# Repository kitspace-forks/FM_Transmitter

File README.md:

# FM Transmitter

This is the circuit built by Afrotechmods in this frequency modulation tutorial video.

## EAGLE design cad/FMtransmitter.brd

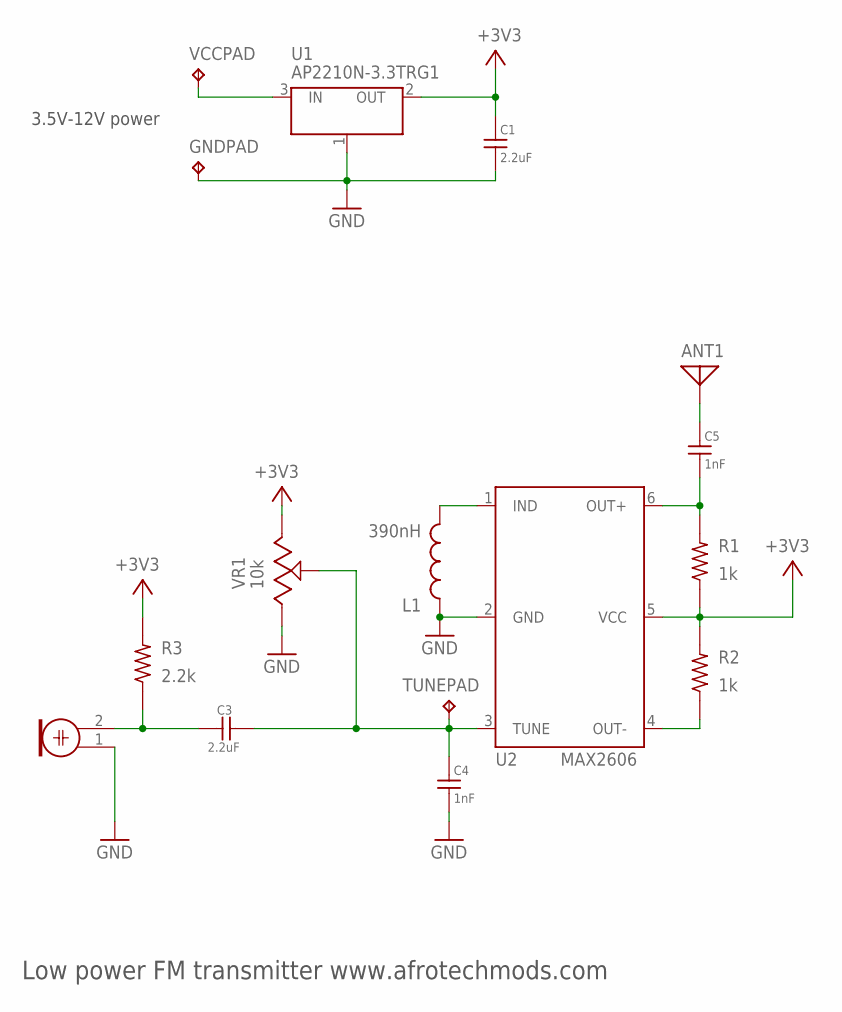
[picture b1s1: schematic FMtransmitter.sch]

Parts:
ANT1: ANTENNA; PAD-01
C1, C3: 2.2uF; 0805
C4, C5: 1nF; 0805
GNDPAD: TPPAD1-13; P1-13
L1: 390nH; 0805
MK1: ELECTRET_MICROPHON-WM-64PC/64PK; WM-64PC/64PK
R1, R2: 1k; 0805
R3: 2.2k; 0805
TUNEPAD: TPPAD1-13; P1-13
U1: AP2210N-3.3TRG1; SOT-23
U2: MAX2606; SOT23-6
VCCPAD: TPPAD1-13; P1-13
VR1: 10k; SMDPOT

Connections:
+3V3: C1.P$2 (2), R1.P$2 (2), R2.P$1 (1), R3.P$1 (1), U1.2 (OUT), U2.5 (VCC), VR1.3 (E)
GND: C1.P$1 (1), C4.P$1 (1), GNDPAD.TP, L1.P$1 (1), MK1.1, U1.1 (GND), U2.2 (GND), VR1.1 (A)
unnamed: L1.P$2 (2), U2.1 (IND)
unnamed: U1.3 (IN), VCCPAD.TP
unnamed: C5.P$1 (1), R1.P$1 (1), U2.6 (OUT+)
unnamed: R2.P$2 (2), U2.4 (OUT-)
unnamed: ANT1.1, C5.P$2 (2)
unnamed: C3.P$2 (2), MK1.2, R3.P$2 (2)
TUNE: C3.P$1 (1), C4.P$2 (2), TUNEPAD.TP, U2.3 (TUNE), VR1.2 (WIPER)

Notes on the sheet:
Low power FM transmitter www.afrotechmods.com
3.5V-12V power

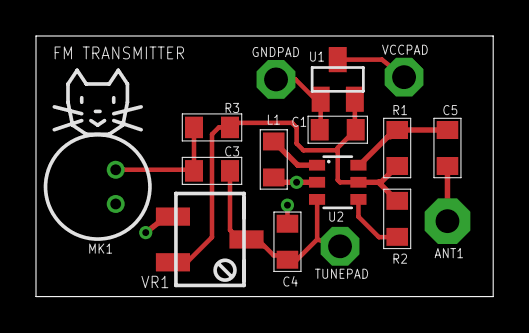
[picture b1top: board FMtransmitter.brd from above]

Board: 2 copper layers, 25.4 x 14.5 mm, 16 parts (0 on the bottom side), 9 nets.

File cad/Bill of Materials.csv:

Qty,Line Item,Manufacturer,MPN,Octopart URL,Schematic Reference,Internal Part Number,Description,Total Qty (@ Batch Size: 1),SKU,SKU,SKU,Packaging,Packaging,Packaging,Unit Price (@ Batch Size: 1),Unit Price (@ Batch Size: 1),Unit Price (@ Batch Size: 1),In Stock,In Stock,In Stock,MOQ,MOQ,MOQ,URL,URL,URL,Distributor [Digi-Key],SKU [Digi-Key],Packaging [Digi-Key],Unit Price (@ Batch Size: 1) [Digi-Key],Line Total [Digi-Key],Batch Total [Digi-Key],In Stock [Digi-Key],MOQ [Digi-Key],URL [Digi-Key],Notes
,,,,,,,,,Digi-Key,Mouser,Newark,Digi-Key,Mouser,Newark,Digi-Key,Mouser,Newark,Digi-Key,Mouser,Newark,Digi-Key,Mouser,Newark,Digi-Key,Mouser,Newark,,,,,,,,,,
1,MAX2606EUT+T,Maxim Integrated,MAX2606EUT+T,https://octopart.com/max2606eut%2Bt-maxim+integrated-42975119,U2,,VCO,1,MAX2606EUT+TCT-ND,MAX2606EUT+T,,Cut Tape,,,2.16,2.12,,1389,1170,,1,,,https://octopart-clicks.com/click/track?country=CA&ak=68b25f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,https://octopart-clicks.com/click/track?country=CA&ak=68b25f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,,Digi-Key,MAX2606EUT+TCT-ND,Cut Tape,2.16,2.16,2.16,1389,1,https://octopart-clicks.com/click/track?country=CA&ak=68b25f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,
2,ERJ-6ENF1001V,Panasonic,ERJ-6ENF1001V,https://octopart.com/erj-6enf1001v-panasonic-55422300,"R1, R2",,1.1k 0805,2,P1.00KCCT-ND,ERJ-6ENF1001V,,Cut Tape,,,0.1,0.11,,1585958,455789,,1,,,https://octopart-clicks.com/click/track?country=CA&ak=68b25f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,https://octopart-clicks.com/click/track?country=CA&ak=68b25f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,,Digi-Key,P1.00KCCT-ND,Cut Tape,0.1,0.2,0.2,1585958,1,https://octopart-clicks.com/click/track?country=CA&ak=68b25f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,
1,LQW2BASR39J00L,Murata,LQW2BASR39J00L,https://octopart.com/lqw2basr39j00l-murata-19973717,L1,,390nH,1,490-5673-1-ND,LQW2BASR39J00L,,Cut Tape,,,0.25,0.25,,5471,2835,,1,,,https://octopart-clicks.com/click/track?country=CA&ak=68b25f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,https://octopart-clicks.com/click/track?country=CA&ak=68b25f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,,Digi-Key,490-5673-1-ND,Cut Tape,0.25,0.25,0.25,5471,1,https://octopart-clicks.com/click/track?country=CA&ak=68b25f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,
1,AP2210N-3.3TRG1,Diodes Inc.,AP2210N-3.3TRG1,https://octopart.com/ap2210n-3.3trg1-diodes+inc.-30954633,U1,,3.3V regulator,1,AP2210N-3.3TRG1DICT-ND,AP2210N-3.3TRG1,,Cut Tape,,,0.42,0.49,,14704,10447,,1,,,https://octopart-clicks.com/click/track?country=CA&ak=68b25f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,https://octopart-clicks.com/click/track?country=CA&ak=68b25f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,,Digi-Key,AP2210N-3.3TRG1DICT-ND,Cut Tape,0.42,0.42,0.42,14704,1,https://octopart-clicks.com/click/track?country=CA&ak=68b25f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,
1,CMC-5042PF-AC,CUI,CMC-5042PF-AC,https://octopart.com/cmc-5042pf-ac-cui-19029063,MK1,,Microphone,1,102-1724-ND,CMC-5042PF-AC,,Bulk,,,1.4,1.39,,13251,3075,,1,,,https://octopart-clicks.com/click/track?country=CA&ak=68b25f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,https://octopart-clicks.com/click/track?country=CA&ak=68b25f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,,Digi-Key,102-1724-ND,Bulk,1.4,1.4,1.4,13251,1,https://octopart-clicks.com/click/track?country=CA&ak=68b25f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,
1,RC0805FR-072K2L,Yageo,RC0805FR-072K2L,https://octopart.com/rc0805fr-072k2l-yageo-40953263,R3,,2.2k 0805,1,311-2.20KCRCT-ND,RC0805FR-072K2L,,Cut Tape,,,0.1,0.1,,153617,44252,,1,,,https://octopart-clicks.com/click/track?country=CA&ak=68b25f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,https://octopart-clicks.com/click/track?country=CA&ak=68b25f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,,Digi-Key,311-2.20KCRCT-ND,Cut Tape,0.1,0.1,0.1,153617,1,https://octopart-clicks.com/click/track?country=CA&ak=68b25f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,
2,CC0805JRNPO9BN102,Yageo,CC0805JRNPO9BN102,https://octopart.com/cc0805jrnpo9bn102-yageo-42250298,"C4, C5",,1nF 0805 NP0,2,311-1122-1-ND,CC0805JRNPO9BN102,,Cut Tape,,,0.1,0.11,,4000,21805,,1,,,https://octopart-clicks.com/click/track?country=CA&ak=68b25f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,https://octopart-clicks.com/click/track?country=CA&ak=68b25f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,,Digi-Key,311-1122-1-ND,Cut Tape,0.1,0.2,0.2,4000,1,https://octopart-clicks.com/click/track?country=CA&ak=68b25f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,
2,CC0805KKX7R7BB225,Yageo,CC0805KKX7R7BB225,https://octopart.com/cc0805kkx7r7bb225-yageo-11543700,"C1, C3",,2.2uF 0805 X7R,2,311-1881-1-ND,CC0805KKX7R7BB225,,Cut Tape,,,0.16,0.15,,2127,30074,,1,,,https://octopart-clicks.com/click/track?country=CA&ak=68b25f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,https://octopart-clicks.com/click/track?country=CA&ak=68b25f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,,Digi-Key,311-1881-1-ND,Cut Tape,0.16,0.32,0.32,2127,1,https://octopart-clicks.com/click/track?country=CA&ak=68b25f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,
1,44WR10KLFT7,BI Technologies,44WR10KLFT7,https://octopart.com/44wr10klft7-bi+technologies-2153410,VR1,,10k pot,1,987-1046-1-ND,44WR10KLFT7,,Cut Tape,,,2.76,2.45,,3043,3155,,1,,,https://octopart-clicks.com/click/track?country=CA&ak=68b25f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,https://octopart-clicks.com/click/track?country=CA&ak=68b25f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,,Digi-Key,987-1046-1-ND,Cut Tape,2.76,2.76,2.76,3043,1,https://octopart-clicks.com/click/track?country=CA&ak=68b25f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,

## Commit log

2016-01-09 Add gerbers, 1-click-BOM and kitnic.yaml
2016-05-25 Update to new kitnic conventions
2016-06-27 Add file-format to drill file to aide rendering
2016-07-01 Rename gto gerber to pls
2018-08-27 Add a readme
